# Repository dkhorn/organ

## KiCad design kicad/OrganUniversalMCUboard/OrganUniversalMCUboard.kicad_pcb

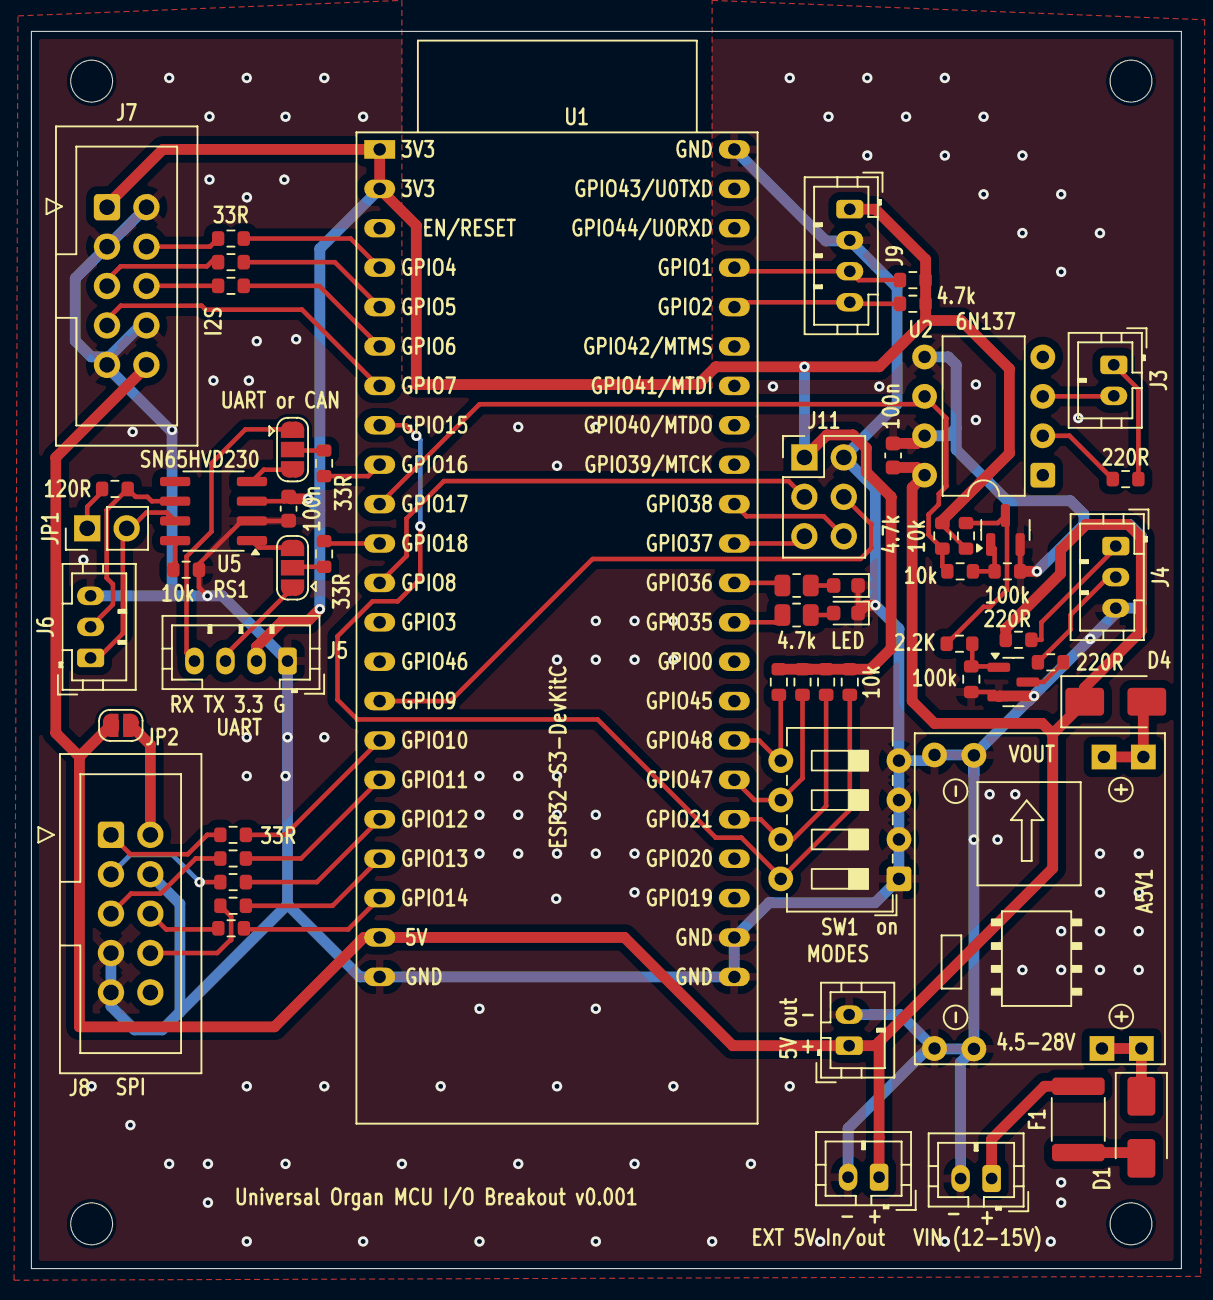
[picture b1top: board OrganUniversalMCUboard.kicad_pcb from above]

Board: 2 copper layers, 74.1 x 79.8 mm, 58 parts (0 on the bottom side), 61 nets.

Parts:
A5V1: 4.7; MP1584EN_Module
CD_U2, CD_U5: 100n; C_0603_1608Metric
D1: SS34; D_SMA
D2, D3: LED; LED_0603_1608Metric
D4: SS14; D_SMA
F1: MF-MSMF050; Fuse_1812_4532Metric
J1: VIN (12-15V); JST_PH_B2B-PH-K_1x02_P2.00mm_Vertical
J2: EXT 5V In/out; JST_PH_B2B-PH-K_1x02_P2.00mm_Vertical
J3: MIDI IN; JST_PH_B2B-PH-K_1x02_P2.00mm_Vertical
J4: MIDI_THRU; JST_PH_B3B-PH-K_1x03_P2.00mm_Vertical
J5: UART; JST_PH_B4B-PH-K_1x04_P2.00mm_Vertical
J6: CAN; JST_PH_B3B-PH-K_1x03_P2.00mm_Vertical
J7: I2S; IDC-Header_2x05_P2.54mm_Vertical
J8: SPI; IDC-Header_2x05_P2.54mm_Vertical
J9: I2C; JST_PH_B4B-PH-K_1x04_P2.00mm_Vertical
J10: 5V out; JST_PH_B2B-PH-K_1x02_P2.00mm_Vertical
J11: GPIO; PinHeader_2x03_P2.54mm_Vertical
JP1: CAN Terminator; PinHeader_1x02_P2.54mm_Vertical
JP2: SolderJumper_2_Open; SolderJumper-2_P1.3mm_Open_RoundedPad1.0x1.5mm
Q1, Q2: MMBT3904; SOT-23
R1, R8: 10k; R_0603_1608Metric
R2, R5, R7: 220R; R_0603_1608Metric
R3: 2.2K; R_0603_1608Metric
R4, R9: 100k; R_0603_1608Metric
R6: 4.7k; R_0603_1608Metric
RLED1, RLED2: 4.7k; R_0805_2012Metric
RP_DIP1, RP_DIP2, RP_DIP3, RP_DIP4: 10k; R_0603_1608Metric
RP_SCL1: 4.7k; R_0603_1608Metric
RP_SDA1: 4.7k; R_0603_1608Metric
RS1: 10k; R_0603_1608Metric
RS_BCLK1: 33R; R_0603_1608Metric
RS_CLR1: 33R; R_0603_1608Metric
RS_DIN1: 33R; R_0603_1608Metric
RS_LATCH1: 33R; R_0603_1608Metric
RS_LRCLK1: 33R; R_0603_1608Metric
RS_MOSI1: 33R; R_0603_1608Metric
RS_OE_N1: 33R; R_0603_1608Metric
RS_SCK1: 33R; R_0603_1608Metric
RS_UART_RX1: 33R; R_0603_1608Metric
RS_UART_TX1: 33R; R_0603_1608Metric
R_TERM1: 120R; R_0603_1608Metric
SJ_COMM_RX1: UART or CAN; SolderJumper-3_P1.3mm_Open_RoundedPad1.0x1.5mm
SJ_COMM_TX1: UART or CAN; SolderJumper-3_P1.3mm_Open_RoundedPad1.0x1.5mm
SW1: MODES; SW_DIP_SPSTx04_Slide_6.7x11.72mm_W7.62mm_P2.54mm_LowProfile
U1: ESP32-S3-DevKitC
U2: 6N137; DIP-8_W7.62mm
U5: SN65HVD230; SOIC-8_3.9x4.9mm_P1.27mm

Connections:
+3.3V: CD_U5.1, J5.2, J7.1, J9.1, J11.1, R6.1, R8.1, RP_DIP1.1, RP_DIP2.1, RP_DIP3.1, RP_DIP4.1, RP_SCL1.1, RP_SDA1.1, U1.1 (3V3), U1.2 (3V3), U5.3 (VCC)
/BoardToBoardComms/CANH: J6.1, JP1.2 (B), U5.7 (CANH)
/BoardToBoardComms/CANL: J6.2, R_TERM1.2, U5.6 (CANL)
/BoardToBoardComms/CAN_RXD: SJ_COMM_RX1.3 (B), U5.4 (R)
/BoardToBoardComms/CAN_TXD: SJ_COMM_TX1.3 (B), U5.1 (D)
/BoardToBoardComms/UART_RX_HDR: J5.4, SJ_COMM_RX1.1 (A)
/BoardToBoardComms/UART_TX_HDR: J5.3, SJ_COMM_TX1.1 (A)
/COMM_RX: RS_UART_RX1.1, U1.9 (GPIO16/ADC2_CH5/32K_N)
/COMM_TX: RS_UART_TX1.1, U1.11 (GPIO18/ADC2_CH7)
/DIP1: RP_DIP1.2, SW1.8, U1.8 (GPIO15/ADC2_CH4/32K_P)
/DIP2: RP_DIP2.2, SW1.7, U1.27 (GPIO21)
/DIP3: RP_DIP3.2, SW1.6, U1.28 (GPIO47)
/DIP4: RP_DIP4.2, SW1.5, U1.29 (GPIO48)
/GPIO8: J11.3, U1.12 (GPIO8/ADC1_CH7)
/GPIO9: J11.4, U1.15 (GPIO9/ADC1_CH8)
/GPIO37: J11.5, U1.34 (GPIO37)
/GPIO38: J11.6, U1.35 (GPIO38)
/I2C_SCL: J9.4, RP_SCL1.2, U1.40 (GPIO2/ADC1_CH1)
/I2C_SDA: J9.3, RP_SDA1.2, U1.41 (GPIO1/ADC1_CH0)
/I2S_BLCK: RS_BCLK1.2, U1.4 (GPIO4/ADC1_CH3)
/I2S_DIN: RS_DIN1.2, U1.6 (GPIO6/ADC1_CH5)
/I2S_LRCLK: RS_LRCLK1.2, U1.5 (GPIO5/ADC1_CH4)
/I2S_MCLK: J7.7, U1.7 (GPIO7/ADC1_CH6)
/LED1: RLED1.1, U1.32 (GPIO35)
/LED2: RLED2.1, U1.33 (GPIO36)
/MIDI/MIDI_IN_P4: J3.1, R5.1
/MIDI/MIDI_IN_P5: J3.2, U2.3 (C)
/MIDI/MIDI_THRU_DRV: Q2.3 (C), R3.1, R8.2
/MIDI/MIDI_THRU_P4: J4.1, R7.2
/MIDI/MIDI_THRU_P5: J4.2, R2.2
/MIDI/MIDI_THRU_SINK: Q1.3 (C), R2.1
/MIDI/Q1_B: Q1.1 (B), R3.2, R4.2
/MIDI_GPIO: R1.1, R6.2, U1.10 (GPIO17/ADC2_CH6), U2.6 (VO)
/Power/BUCK_5V: A5V1.3 (OUT+), D4.2 (A)
/Power/VIN_12V: F1.2, J1.1
/Power/VIN_FUSED: D1.2 (A), F1.1
/Power/VIN_PROT: A5V1.1 (IN+), D1.1 (K)
/SPI_CLR: RS_CLR1.2, U1.16 (GPIO10/ADC1_CH9)
/SPI_LATCH: RS_LATCH1.2, U1.20 (GPIO14/ADC2_CH3)
/SPI_MOSI: RS_MOSI1.2, U1.19 (GPIO13/ADC2_CH2)
/SPI_OE_N: RS_OE_N1.2, U1.17 (GPIO11/ADC2_CH0)
/SPI_SCK: RS_SCK1.2, U1.18 (GPIO12/ADC2_CH1)
GND: A5V1.2 (IN-), A5V1.4 (OUT-), CD_U2.2, CD_U5.2, D2.1 (K), D3.1 (K), J1.2, J2.2, J4.3, J5.1, J6.3, J7.2, J7.3, J7.8, J7.9, J8.4, J8.7, J8.9, J9.2, J10.2, J11.2, Q1.2 (E), Q2.2 (E), R4.1, R9.1, RS1.2, SW1.1, SW1.2, SW1.3, SW1.4, U1.22 (GND), U1.23 (GND), U1.24 (GND), U1.44 (GND), U2.5 (GND), U2.7 (EN), U5.2 (GND)
unnamed: D2.2 (A), RLED1.2
unnamed: D3.2 (A), RLED2.2
unnamed: J7.4, RS_BCLK1.1
unnamed: J7.5, RS_LRCLK1.1
unnamed: J7.6, RS_DIN1.1
unnamed: J8.1, RS_CLR1.1
unnamed: J8.2, JP2.1 (A)
unnamed: J8.3, RS_SCK1.1
unnamed: J8.5, RS_OE_N1.1
unnamed: J8.6, RS_LATCH1.1
unnamed: J8.8, RS_MOSI1.1
unnamed: JP1.1 (A), R_TERM1.1
unnamed: Q2.1 (B), R1.2, R9.2
unnamed: RS_UART_RX1.2, SJ_COMM_RX1.2 (C)
unnamed: RS_UART_TX1.2, SJ_COMM_TX1.2 (C)
unnamed: R5.2, U2.2 (A)
unnamed: RS1.1, U5.8 (Rs)
SYS_5V: CD_U2.1, D4.1 (K), J2.1, J7.10, J10.1, JP2.2 (B), R7.1, U1.21 (5V), U2.8 (VCC)

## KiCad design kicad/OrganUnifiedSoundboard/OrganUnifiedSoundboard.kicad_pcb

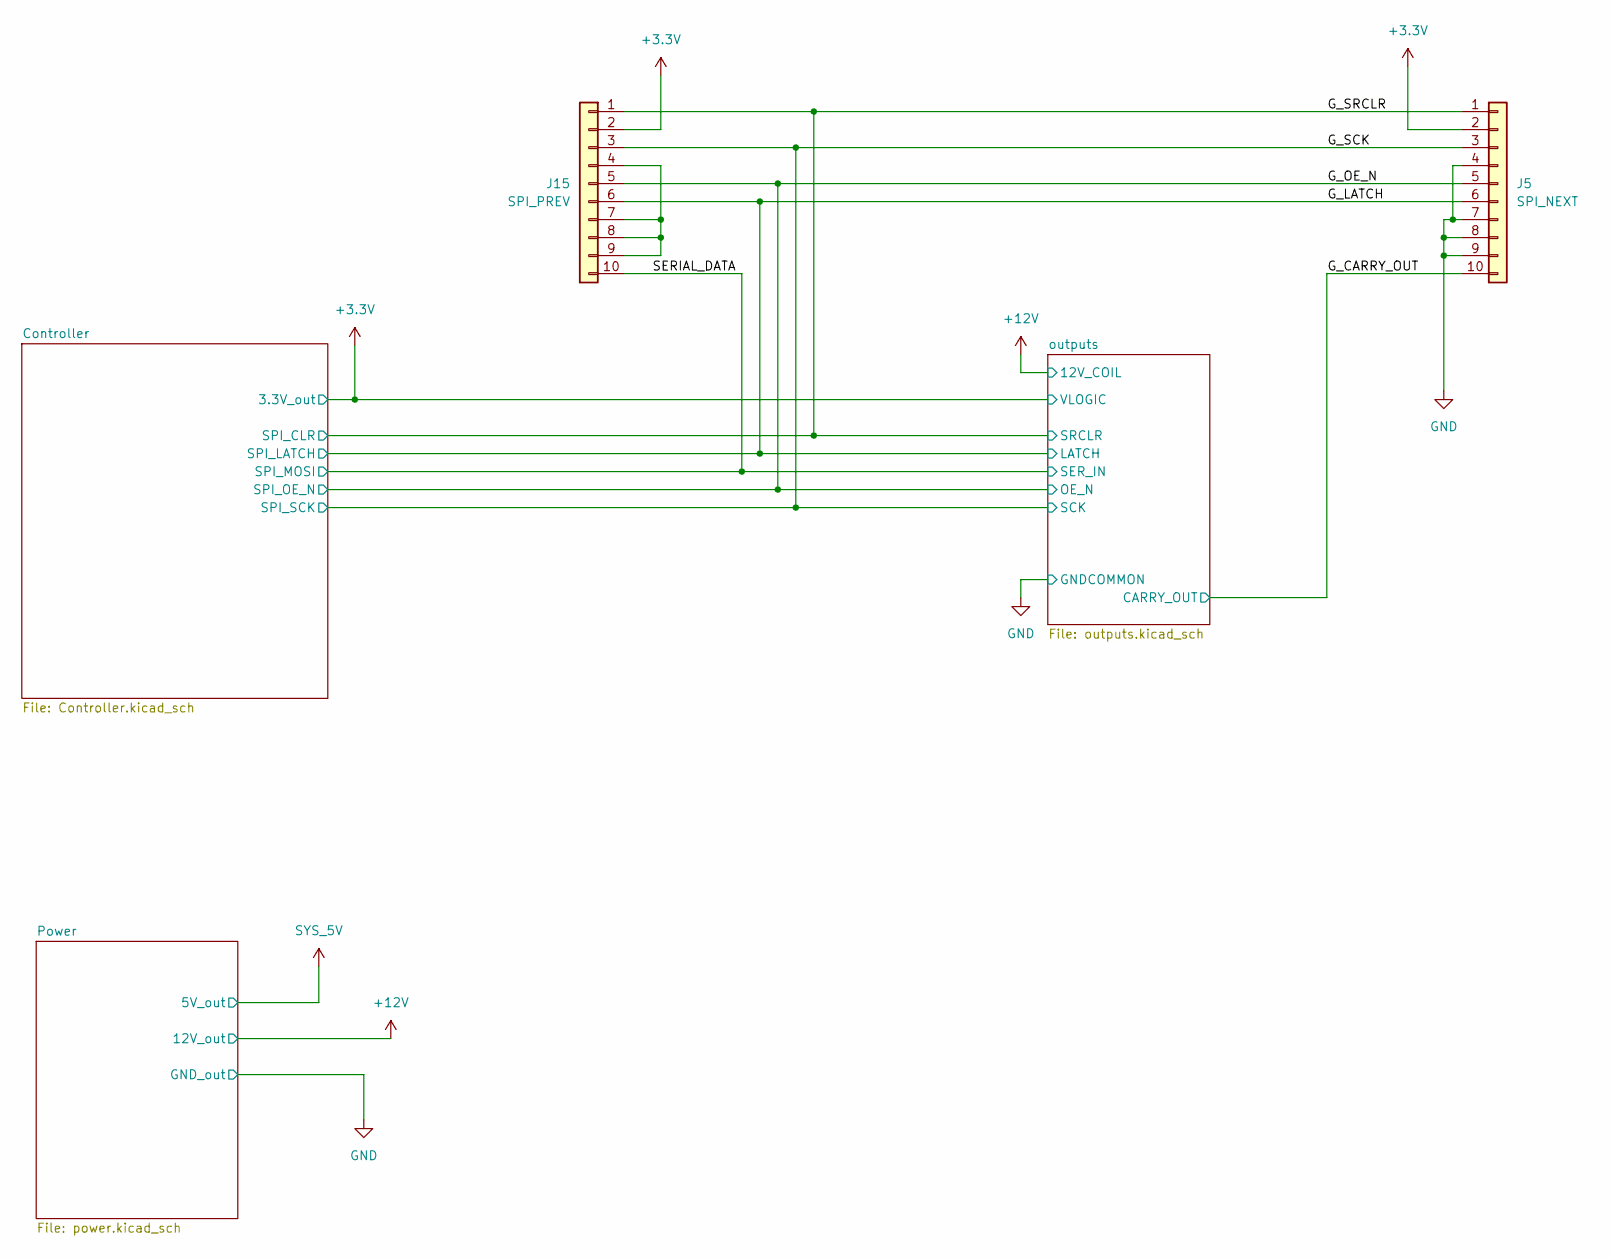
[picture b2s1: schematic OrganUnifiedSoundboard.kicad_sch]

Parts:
J5: SPI_NEXT; IDC-Header_2x05_P2.54mm_Vertical
J15: SPI_PREV; IDC-Header_2x05_P2.54mm_Vertical

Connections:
+3.3V: J5.2, J15.2; also elsewhere on the board
/G_CARRY_OUT: J5.10; also elsewhere on the board
/G_LATCH: J5.6, J15.6; also elsewhere on the board
/G_OE_N: J5.5, J15.5; also elsewhere on the board
/G_SCK: J5.3, J15.3; also elsewhere on the board
/G_SRCLR: J5.1, J15.1; also elsewhere on the board
/SERIAL_DATA: J15.10; also elsewhere on the board
GND: J5.4, J5.7, J5.8, J5.9; also elsewhere on the board
unnamed: J15.4, J15.7, J15.8, J15.9

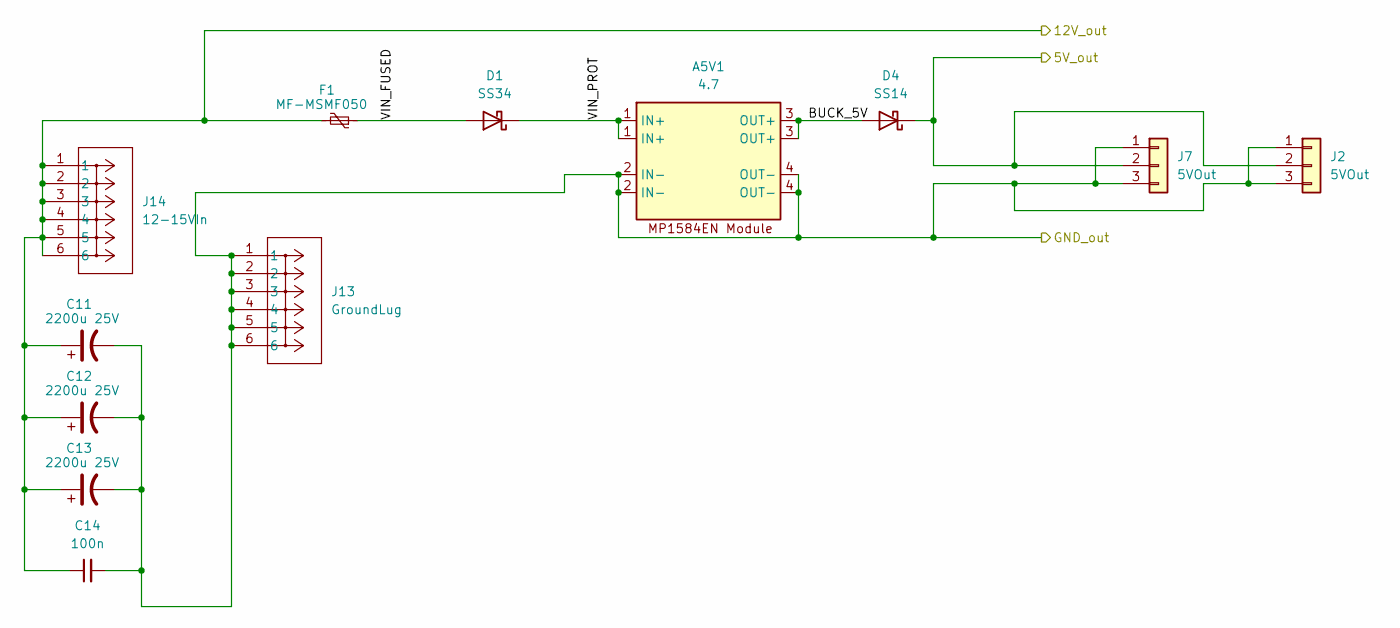
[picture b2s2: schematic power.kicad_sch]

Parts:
A5V1: 4.7; MP1584EN_Module
C11, C12, C13: 2200u 25V; CP_Radial_D10.0mm_P5.00mm
C14: 100n; C_0603_1608Metric
D1: SS34; D_SMA
D4: SS14; D_SMA
F1: MF-MSMF050; Fuse_1812_4532Metric
J2, J7: 5VOut; JST_PH_B3B-PH-K_1x03_P2.00mm_Vertical
J13: GroundLug; CONN_8199_KEY
J14: 12-15VIn; CONN_8199_KEY

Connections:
+12V: C11.1, C12.1, C13.1, C14.1, F1.2, J14.1, J14.2, J14.3, J14.4, J14.5, J14.6; also elsewhere on the board
/Power/BUCK_5V: A5V1.3 (OUT+), D4.2 (A)
/Power/VIN_FUSED: D1.2 (A), F1.1
/Power/VIN_PROT: A5V1.1 (IN+), D1.1 (K)
GND: A5V1.2 (IN-), A5V1.4 (OUT-), C11.2, C12.2, C13.2, C14.2, J2.1, J2.3, J7.1, J7.3, J13.1, J13.2, J13.3, J13.4, J13.5, J13.6; also elsewhere on the board
SYS_5V: D4.1 (K), J2.2, J7.2; also elsewhere on the board

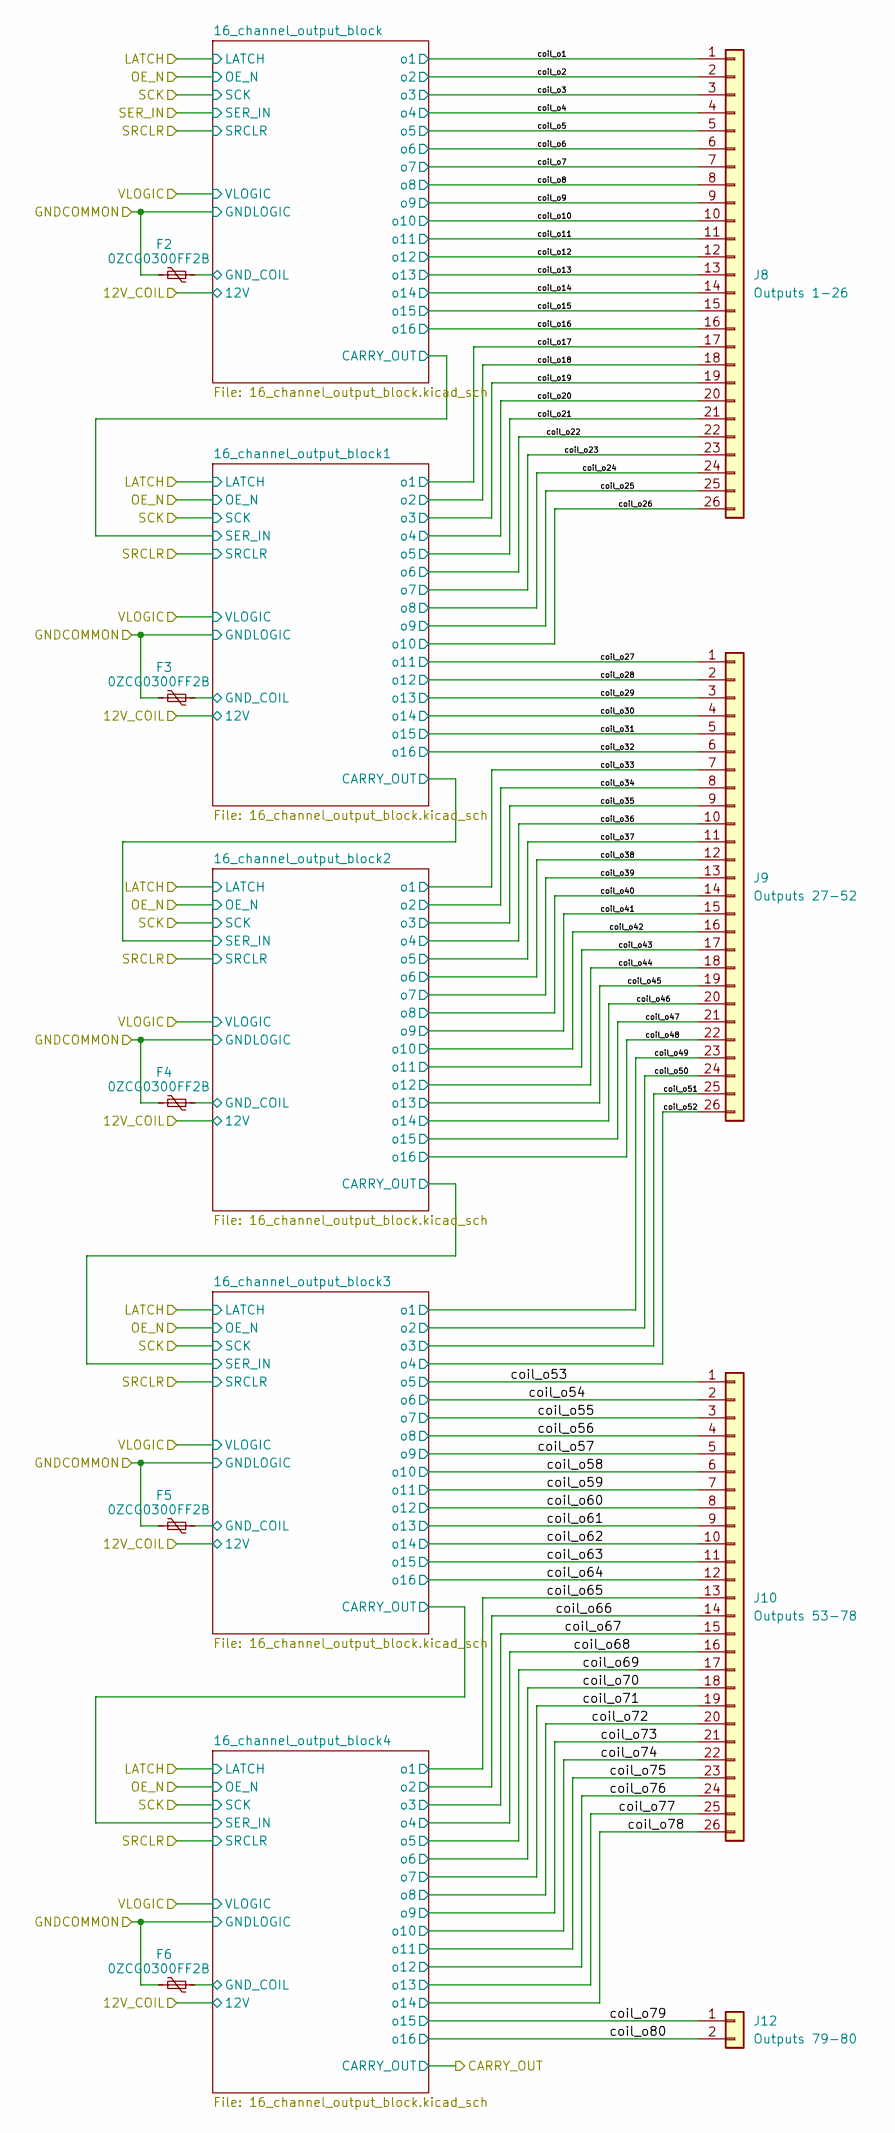
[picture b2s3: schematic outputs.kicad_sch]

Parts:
F2, F3, F4, F5, F6: 0ZCG0300FF2B; Fuse_1812_4532Metric
J8: Outputs 1-26; IDC-Header_2x13_P2.54mm_Vertical
J9: Outputs 27-52; IDC-Header_2x13_P2.54mm_Vertical
J10: Outputs 53-78; IDC-Header_2x13_P2.54mm_Vertical
J12: Outputs 79-80; JST_PH_B2B-PH-K_1x02_P2.00mm_Vertical

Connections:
/outputs/16_channel_output_block1/GND_COIL: F3.1; also elsewhere on the board
/outputs/16_channel_output_block2/GND_COIL: F4.1; also elsewhere on the board
/outputs/16_channel_output_block3/GND_COIL: F5.1; also elsewhere on the board
/outputs/16_channel_output_block4/GND_COIL: F6.1; also elsewhere on the board
/outputs/16_channel_output_block/GND_COIL: F2.1; also elsewhere on the board
/outputs/coil_o1: J8.1; also elsewhere on the board
/outputs/coil_o2: J8.2; also elsewhere on the board
/outputs/coil_o3: J8.3; also elsewhere on the board
/outputs/coil_o4: J8.4; also elsewhere on the board
/outputs/coil_o5: J8.5; also elsewhere on the board
/outputs/coil_o6: J8.6; also elsewhere on the board
/outputs/coil_o7: J8.7; also elsewhere on the board
/outputs/coil_o8: J8.8; also elsewhere on the board
/outputs/coil_o9: J8.9; also elsewhere on the board
/outputs/coil_o10: J8.10; also elsewhere on the board
/outputs/coil_o11: J8.11; also elsewhere on the board
/outputs/coil_o12: J8.12; also elsewhere on the board
/outputs/coil_o13: J8.13; also elsewhere on the board
/outputs/coil_o14: J8.14; also elsewhere on the board
/outputs/coil_o15: J8.15; also elsewhere on the board
/outputs/coil_o16: J8.16; also elsewhere on the board
/outputs/coil_o17: J8.17; also elsewhere on the board
/outputs/coil_o18: J8.18; also elsewhere on the board
/outputs/coil_o19: J8.19; also elsewhere on the board
/outputs/coil_o20: J8.20; also elsewhere on the board
/outputs/coil_o21: J8.21; also elsewhere on the board
/outputs/coil_o22: J8.22; also elsewhere on the board
/outputs/coil_o23: J8.23; also elsewhere on the board
/outputs/coil_o24: J8.24; also elsewhere on the board
/outputs/coil_o25: J8.25; also elsewhere on the board
/outputs/coil_o26: J8.26; also elsewhere on the board
/outputs/coil_o27: J9.1; also elsewhere on the board
/outputs/coil_o28: J9.2; also elsewhere on the board
/outputs/coil_o29: J9.3; also elsewhere on the board
/outputs/coil_o30: J9.4; also elsewhere on the board
/outputs/coil_o31: J9.5; also elsewhere on the board
/outputs/coil_o32: J9.6; also elsewhere on the board
/outputs/coil_o33: J9.7; also elsewhere on the board
/outputs/coil_o34: J9.8; also elsewhere on the board
/outputs/coil_o35: J9.9; also elsewhere on the board
/outputs/coil_o36: J9.10; also elsewhere on the board
/outputs/coil_o37: J9.11; also elsewhere on the board
/outputs/coil_o38: J9.12; also elsewhere on the board
/outputs/coil_o39: J9.13; also elsewhere on the board
/outputs/coil_o40: J9.14; also elsewhere on the board
/outputs/coil_o41: J9.15; also elsewhere on the board
/outputs/coil_o42: J9.16; also elsewhere on the board
/outputs/coil_o43: J9.17; also elsewhere on the board
/outputs/coil_o44: J9.18; also elsewhere on the board
/outputs/coil_o45: J9.19; also elsewhere on the board
/outputs/coil_o46: J9.20; also elsewhere on the board
/outputs/coil_o47: J9.21; also elsewhere on the board
/outputs/coil_o48: J9.22; also elsewhere on the board
/outputs/coil_o49: J9.23; also elsewhere on the board
/outputs/coil_o50: J9.24; also elsewhere on the board
/outputs/coil_o51: J9.25; also elsewhere on the board
/outputs/coil_o52: J9.26; also elsewhere on the board
/outputs/coil_o53: J10.1; also elsewhere on the board
/outputs/coil_o54: J10.2; also elsewhere on the board
/outputs/coil_o55: J10.3; also elsewhere on the board
/outputs/coil_o56: J10.4; also elsewhere on the board
/outputs/coil_o57: J10.5; also elsewhere on the board
/outputs/coil_o58: J10.6; also elsewhere on the board
/outputs/coil_o59: J10.7; also elsewhere on the board
/outputs/coil_o60: J10.8; also elsewhere on the board
/outputs/coil_o61: J10.9; also elsewhere on the board
/outputs/coil_o62: J10.10; also elsewhere on the board
/outputs/coil_o63: J10.11; also elsewhere on the board
/outputs/coil_o64: J10.12; also elsewhere on the board
/outputs/coil_o65: J10.13; also elsewhere on the board
/outputs/coil_o66: J10.14; also elsewhere on the board
/outputs/coil_o67: J10.15; also elsewhere on the board
/outputs/coil_o68: J10.16; also elsewhere on the board
/outputs/coil_o69: J10.17; also elsewhere on the board
/outputs/coil_o70: J10.18; also elsewhere on the board
/outputs/coil_o71: J10.19; also elsewhere on the board
/outputs/coil_o72: J10.20; also elsewhere on the board
/outputs/coil_o73: J10.21; also elsewhere on the board
/outputs/coil_o74: J10.22; also elsewhere on the board
/outputs/coil_o75: J10.23; also elsewhere on the board
/outputs/coil_o76: J10.24; also elsewhere on the board
/outputs/coil_o77: J10.25; also elsewhere on the board
/outputs/coil_o78: J10.26; also elsewhere on the board
/outputs/coil_o79: J12.1; also elsewhere on the board
/outputs/coil_o80: J12.2; also elsewhere on the board
GND: F2.2, F3.2, F4.2, F5.2, F6.2; also elsewhere on the board

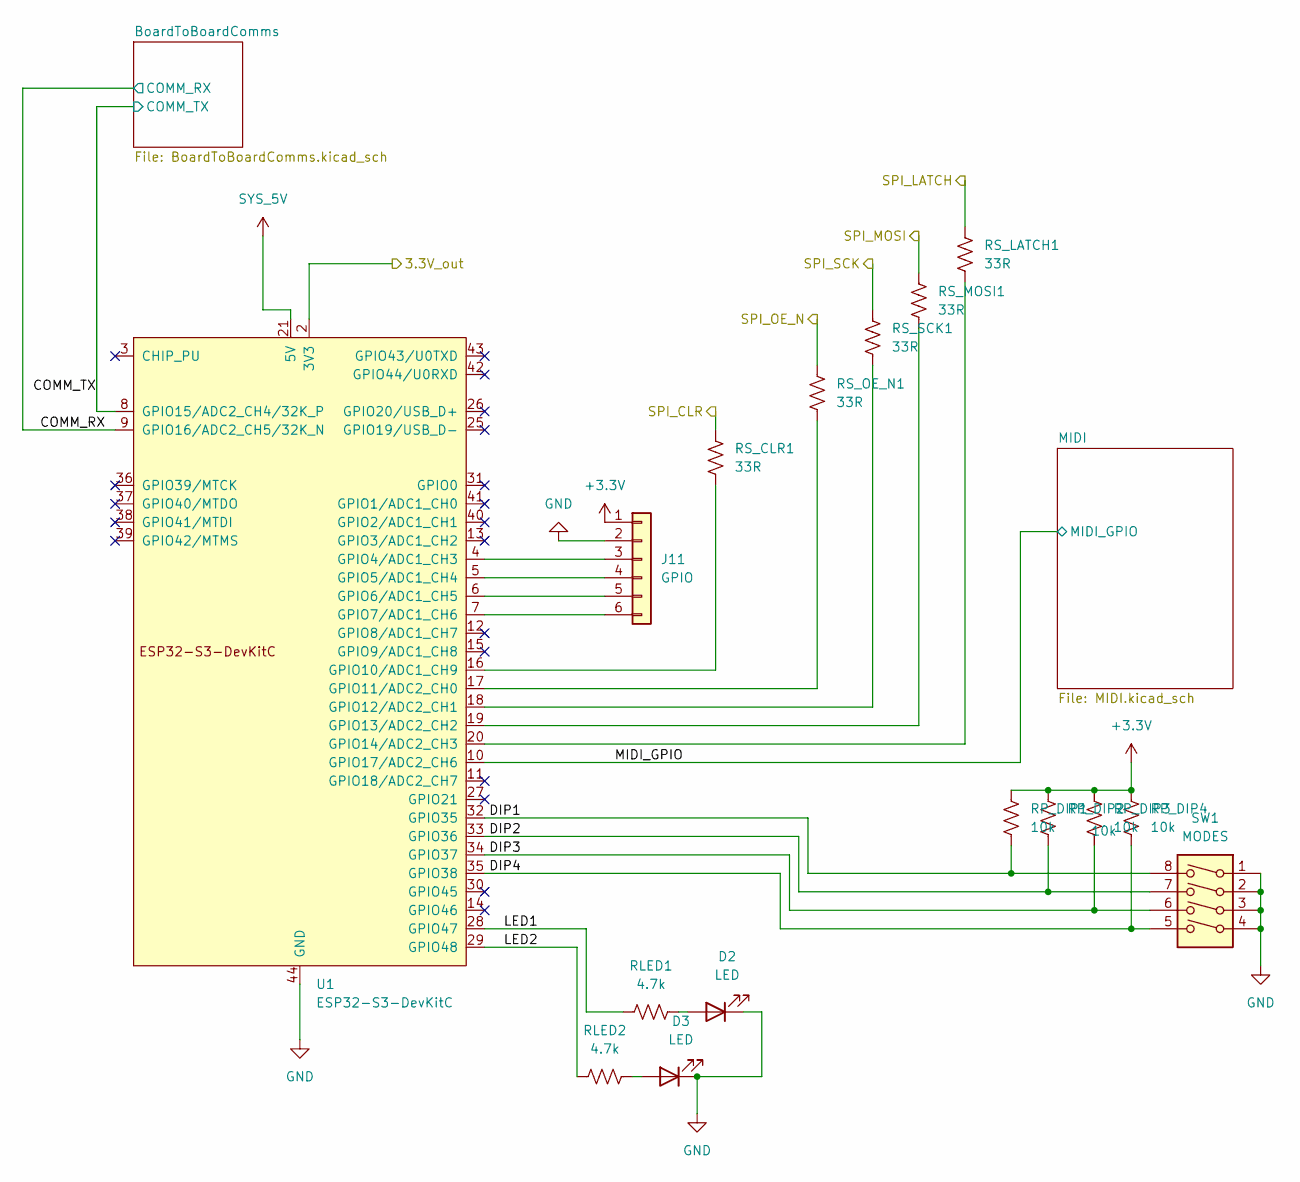
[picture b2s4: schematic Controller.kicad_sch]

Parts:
D2, D3: LED; LED_0603_1608Metric
J11: GPIO; PinHeader_2x03_P2.54mm_Vertical
RLED1, RLED2: 4.7k; R_0805_2012Metric
RP_DIP1, RP_DIP2, RP_DIP3, RP_DIP4: 10k; R_0603_1608Metric
RS_CLR1: 33R; R_0603_1608Metric
RS_LATCH1: 33R; R_0603_1608Metric
RS_MOSI1: 33R; R_0603_1608Metric
RS_OE_N1: 33R; R_0603_1608Metric
RS_SCK1: 33R; R_0603_1608Metric
SW1: MODES; SW_DIP_SPSTx04_Slide_6.7x11.72mm_W7.62mm_P2.54mm_LowProfile
U1: ESP32-S3-DevKitC

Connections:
+3.3V: J11.1, RP_DIP1.1, RP_DIP2.1, RP_DIP3.1, RP_DIP4.1, U1.1 (3V3), U1.2 (3V3); also elsewhere on the board
/Controller/COMM_RX: U1.9 (GPIO16/ADC2_CH5/32K_N); also elsewhere on the board
/Controller/COMM_TX: U1.8 (GPIO15/ADC2_CH4/32K_P); also elsewhere on the board
/Controller/DIP1: RP_DIP1.2, SW1.8, U1.32 (GPIO35)
/Controller/DIP2: RP_DIP2.2, SW1.7, U1.33 (GPIO36)
/Controller/DIP3: RP_DIP3.2, SW1.6, U1.34 (GPIO37)
/Controller/DIP4: RP_DIP4.2, SW1.5, U1.35 (GPIO38)
/Controller/LED1: RLED1.1, U1.28 (GPIO47)
/Controller/LED2: RLED2.1, U1.29 (GPIO48)
/Controller/MIDI_GPIO: U1.10 (GPIO17/ADC2_CH6); also elsewhere on the board
/G_LATCH: RS_LATCH1.1; also elsewhere on the board
/G_OE_N: RS_OE_N1.1; also elsewhere on the board
/G_SCK: RS_SCK1.1; also elsewhere on the board
/G_SRCLR: RS_CLR1.1; also elsewhere on the board
/SERIAL_DATA: RS_MOSI1.1; also elsewhere on the board
GND: D2.1 (K), D3.1 (K), J11.2, SW1.1, SW1.2, SW1.3, SW1.4, U1.22 (GND), U1.23 (GND), U1.24 (GND), U1.44 (GND); also elsewhere on the board
unnamed: D2.2 (A), RLED1.2
unnamed: D3.2 (A), RLED2.2
unnamed: J11.3, U1.4 (GPIO4/ADC1_CH3)
unnamed: J11.4, U1.5 (GPIO5/ADC1_CH4)
unnamed: J11.5, U1.6 (GPIO6/ADC1_CH5)
unnamed: J11.6, U1.7 (GPIO7/ADC1_CH6)
unnamed: RS_CLR1.2, U1.16 (GPIO10/ADC1_CH9)
unnamed: RS_OE_N1.2, U1.17 (GPIO11/ADC2_CH0)
unnamed: RS_SCK1.2, U1.18 (GPIO12/ADC2_CH1)
unnamed: RS_MOSI1.2, U1.19 (GPIO13/ADC2_CH2)
unnamed: RS_LATCH1.2, U1.20 (GPIO14/ADC2_CH3)
SYS_5V: U1.21 (5V); also elsewhere on the board

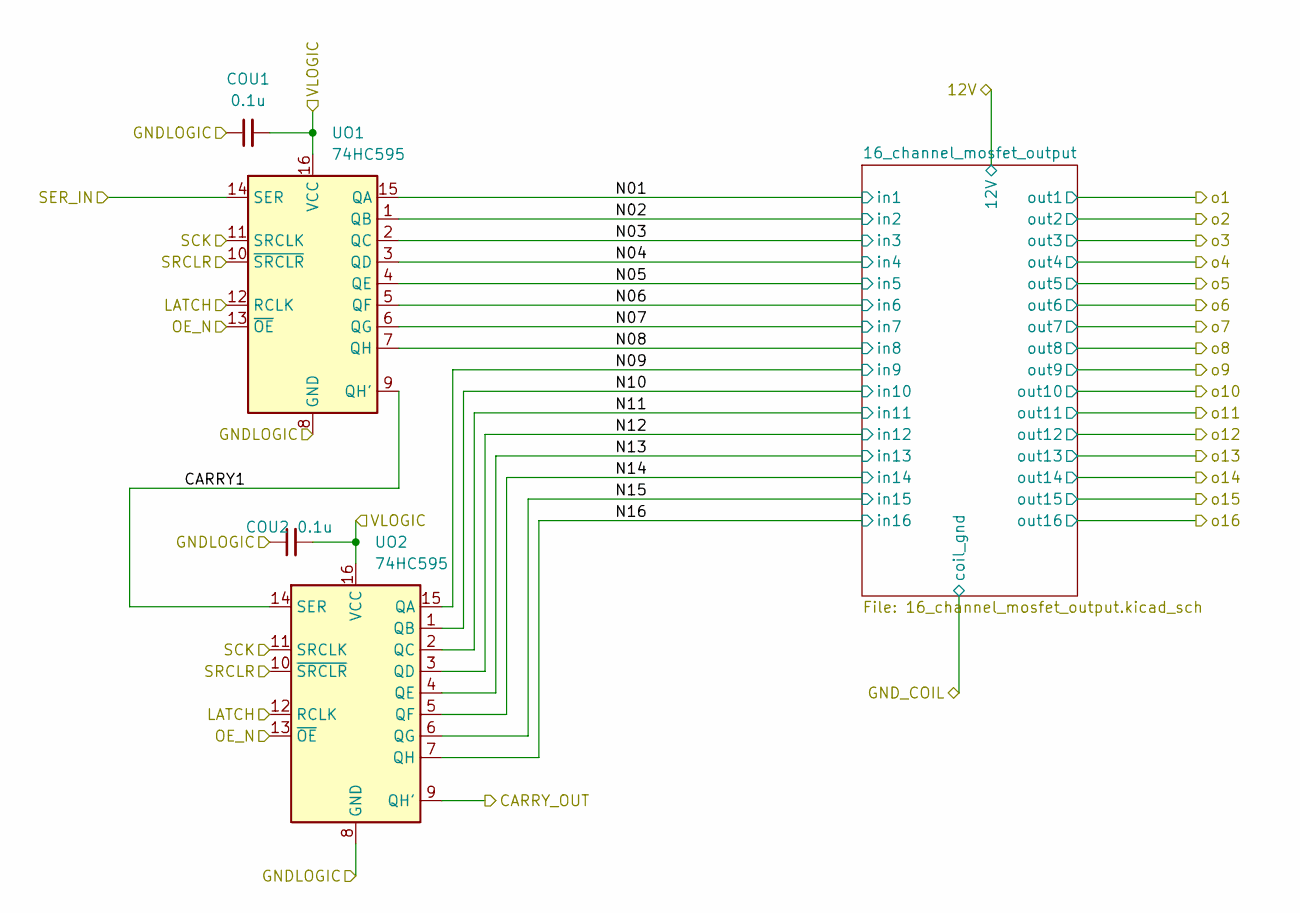
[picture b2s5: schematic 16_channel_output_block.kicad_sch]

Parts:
COU1, COU2: 0.1u; C_0805_2012Metric
UO1, UO2: 74HC595; SOP-16_3.9x9.9mm_P1.27mm

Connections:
+3.3V: COU1.2, COU2.2, UO1.16 (VCC), UO2.16 (VCC); also elsewhere on the board
/G_LATCH: UO1.12 (RCLK), UO2.12 (RCLK); also elsewhere on the board
/G_OE_N: UO1.13 (~OE), UO2.13 (~OE); also elsewhere on the board
/G_SCK: UO1.11 (SRCLK), UO2.11 (SRCLK); also elsewhere on the board
/G_SRCLR: UO1.10 (~SRCLR), UO2.10 (~SRCLR); also elsewhere on the board
/SERIAL_DATA: UO1.14 (SER); also elsewhere on the board
/outputs/16_channel_output_block/CARRY1: UO1.9 (QH'), UO2.14 (SER)
/outputs/16_channel_output_block/CARRY_OUT: UO2.9 (QH'); also elsewhere on the board
/outputs/16_channel_output_block/N01: UO1.15 (QA); also elsewhere on the board
/outputs/16_channel_output_block/N02: UO1.1 (QB); also elsewhere on the board
/outputs/16_channel_output_block/N03: UO1.2 (QC); also elsewhere on the board
/outputs/16_channel_output_block/N04: UO1.3 (QD); also elsewhere on the board
/outputs/16_channel_output_block/N05: UO1.4 (QE); also elsewhere on the board
/outputs/16_channel_output_block/N06: UO1.5 (QF); also elsewhere on the board
/outputs/16_channel_output_block/N07: UO1.6 (QG); also elsewhere on the board
/outputs/16_channel_output_block/N08: UO1.7 (QH); also elsewhere on the board
/outputs/16_channel_output_block/N09: UO2.15 (QA); also elsewhere on the board
/outputs/16_channel_output_block/N10: UO2.1 (QB); also elsewhere on the board
/outputs/16_channel_output_block/N11: UO2.2 (QC); also elsewhere on the board
/outputs/16_channel_output_block/N12: UO2.3 (QD); also elsewhere on the board
/outputs/16_channel_output_block/N13: UO2.4 (QE); also elsewhere on the board
/outputs/16_channel_output_block/N14: UO2.5 (QF); also elsewhere on the board
/outputs/16_channel_output_block/N15: UO2.6 (QG); also elsewhere on the board
/outputs/16_channel_output_block/N16: UO2.7 (QH); also elsewhere on the board
GND: COU1.1, COU2.1, UO1.8 (GND), UO2.8 (GND); also elsewhere on the board

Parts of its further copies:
COU3, COU4, COU5, COU6, COU7, COU8, COU9, COU10: 0.1u; C_0805_2012Metric
UO3, UO4, UO5, UO6, UO7, UO8, UO9, UO10: 74HC595; SOP-16_3.9x9.9mm_P1.27mm

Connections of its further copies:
+3.3V: COU3.2, COU4.2, COU5.2, COU6.2, COU7.2, COU8.2, COU9.2, COU10.2, UO3.16 (VCC), UO4.16 (VCC), UO5.16 (VCC), UO6.16 (VCC), UO7.16 (VCC), UO8.16 (VCC), UO9.16 (VCC), UO10.16 (VCC); also elsewhere on the board
/G_CARRY_OUT: UO10.9 (QH'); also elsewhere on the board
/G_LATCH: UO3.12 (RCLK), UO4.12 (RCLK), UO5.12 (RCLK), UO6.12 (RCLK), UO7.12 (RCLK), UO8.12 (RCLK), UO9.12 (RCLK), UO10.12 (RCLK); also elsewhere on the board
/G_OE_N: UO3.13 (~OE), UO4.13 (~OE), UO5.13 (~OE), UO6.13 (~OE), UO7.13 (~OE), UO8.13 (~OE), UO9.13 (~OE), UO10.13 (~OE); also elsewhere on the board
/G_SCK: UO3.11 (SRCLK), UO4.11 (SRCLK), UO5.11 (SRCLK), UO6.11 (SRCLK), UO7.11 (SRCLK), UO8.11 (SRCLK), UO9.11 (SRCLK), UO10.11 (SRCLK); also elsewhere on the board
/G_SRCLR: UO3.10 (~SRCLR), UO4.10 (~SRCLR), UO5.10 (~SRCLR), UO6.10 (~SRCLR), UO7.10 (~SRCLR), UO8.10 (~SRCLR), UO9.10 (~SRCLR), UO10.10 (~SRCLR); also elsewhere on the board
/outputs/16_channel_output_block1/CARRY1: UO3.9 (QH'), UO4.14 (SER)
/outputs/16_channel_output_block1/CARRY_OUT: UO4.9 (QH'), UO5.14 (SER)
/outputs/16_channel_output_block1/N01: UO3.15 (QA); also elsewhere on the board
/outputs/16_channel_output_block1/N02: UO3.1 (QB); also elsewhere on the board
/outputs/16_channel_output_block1/N03: UO3.2 (QC); also elsewhere on the board
/outputs/16_channel_output_block1/N04: UO3.3 (QD); also elsewhere on the board
/outputs/16_channel_output_block1/N05: UO3.4 (QE); also elsewhere on the board
/outputs/16_channel_output_block1/N06: UO3.5 (QF); also elsewhere on the board
/outputs/16_channel_output_block1/N07: UO3.6 (QG); also elsewhere on the board
/outputs/16_channel_output_block1/N08: UO3.7 (QH); also elsewhere on the board
/outputs/16_channel_output_block1/N09: UO4.15 (QA); also elsewhere on the board
/outputs/16_channel_output_block1/N10: UO4.1 (QB); also elsewhere on the board
/outputs/16_channel_output_block1/N11: UO4.2 (QC); also elsewhere on the board
/outputs/16_channel_output_block1/N12: UO4.3 (QD); also elsewhere on the board
/outputs/16_channel_output_block1/N13: UO4.4 (QE); also elsewhere on the board
/outputs/16_channel_output_block1/N14: UO4.5 (QF); also elsewhere on the board
/outputs/16_channel_output_block1/N15: UO4.6 (QG); also elsewhere on the board
/outputs/16_channel_output_block1/N16: UO4.7 (QH); also elsewhere on the board
/outputs/16_channel_output_block2/CARRY1: UO5.9 (QH'), UO6.14 (SER)
/outputs/16_channel_output_block2/CARRY_OUT: UO6.9 (QH'), UO7.14 (SER)
/outputs/16_channel_output_block2/N01: UO5.15 (QA); also elsewhere on the board
/outputs/16_channel_output_block2/N02: UO5.1 (QB); also elsewhere on the board
/outputs/16_channel_output_block2/N03: UO5.2 (QC); also elsewhere on the board
/outputs/16_channel_output_block2/N04: UO5.3 (QD); also elsewhere on the board
/outputs/16_channel_output_block2/N05: UO5.4 (QE); also elsewhere on the board
/outputs/16_channel_output_block2/N06: UO5.5 (QF); also elsewhere on the board
/outputs/16_channel_output_block2/N07: UO5.6 (QG); also elsewhere on the board
/outputs/16_channel_output_block2/N08: UO5.7 (QH); also elsewhere on the board
/outputs/16_channel_output_block2/N09: UO6.15 (QA); also elsewhere on the board
/outputs/16_channel_output_block2/N10: UO6.1 (QB); also elsewhere on the board
/outputs/16_channel_output_block2/N11: UO6.2 (QC); also elsewhere on the board
/outputs/16_channel_output_block2/N12: UO6.3 (QD); also elsewhere on the board
/outputs/16_channel_output_block2/N13: UO6.4 (QE); also elsewhere on the board
/outputs/16_channel_output_block2/N14: UO6.5 (QF); also elsewhere on the board
/outputs/16_channel_output_block2/N15: UO6.6 (QG); also elsewhere on the board
/outputs/16_channel_output_block2/N16: UO6.7 (QH); also elsewhere on the board
/outputs/16_channel_output_block3/CARRY1: UO7.9 (QH'), UO8.14 (SER)
/outputs/16_channel_output_block3/CARRY_OUT: UO8.9 (QH'), UO9.14 (SER)
/outputs/16_channel_output_block3/N01: UO7.15 (QA); also elsewhere on the board
/outputs/16_channel_output_block3/N02: UO7.1 (QB); also elsewhere on the board
/outputs/16_channel_output_block3/N03: UO7.2 (QC); also elsewhere on the board
/outputs/16_channel_output_block3/N04: UO7.3 (QD); also elsewhere on the board
/outputs/16_channel_output_block3/N05: UO7.4 (QE); also elsewhere on the board
/outputs/16_channel_output_block3/N06: UO7.5 (QF); also elsewhere on the board
/outputs/16_channel_output_block3/N07: UO7.6 (QG); also elsewhere on the board
/outputs/16_channel_output_block3/N08: UO7.7 (QH); also elsewhere on the board
/outputs/16_channel_output_block3/N09: UO8.15 (QA); also elsewhere on the board
/outputs/16_channel_output_block3/N10: UO8.1 (QB); also elsewhere on the board
/outputs/16_channel_output_block3/N11: UO8.2 (QC); also elsewhere on the board
/outputs/16_channel_output_block3/N12: UO8.3 (QD); also elsewhere on the board
/outputs/16_channel_output_block3/N13: UO8.4 (QE); also elsewhere on the board
/outputs/16_channel_output_block3/N14: UO8.5 (QF); also elsewhere on the board
/outputs/16_channel_output_block3/N15: UO8.6 (QG); also elsewhere on the board
/outputs/16_channel_output_block3/N16: UO8.7 (QH); also elsewhere on the board
/outputs/16_channel_output_block4/CARRY1: UO9.9 (QH'), UO10.14 (SER)
/outputs/16_channel_output_block4/N01: UO9.15 (QA); also elsewhere on the board
/outputs/16_channel_output_block4/N02: UO9.1 (QB); also elsewhere on the board
/outputs/16_channel_output_block4/N03: UO9.2 (QC); also elsewhere on the board
/outputs/16_channel_output_block4/N04: UO9.3 (QD); also elsewhere on the board
/outputs/16_channel_output_block4/N05: UO9.4 (QE); also elsewhere on the board
/outputs/16_channel_output_block4/N06: UO9.5 (QF); also elsewhere on the board
/outputs/16_channel_output_block4/N07: UO9.6 (QG); also elsewhere on the board
/outputs/16_channel_output_block4/N08: UO9.7 (QH); also elsewhere on the board
/outputs/16_channel_output_block4/N09: UO10.15 (QA); also elsewhere on the board
/outputs/16_channel_output_block4/N10: UO10.1 (QB); also elsewhere on the board
/outputs/16_channel_output_block4/N11: UO10.2 (QC); also elsewhere on the board
/outputs/16_channel_output_block4/N12: UO10.3 (QD); also elsewhere on the board
/outputs/16_channel_output_block4/N13: UO10.4 (QE); also elsewhere on the board
/outputs/16_channel_output_block4/N14: UO10.5 (QF); also elsewhere on the board
/outputs/16_channel_output_block4/N15: UO10.6 (QG); also elsewhere on the board
/outputs/16_channel_output_block4/N16: UO10.7 (QH); also elsewhere on the board
/outputs/16_channel_output_block/CARRY_OUT: UO3.14 (SER); also elsewhere on the board
GND: COU3.1, COU4.1, COU5.1, COU6.1, COU7.1, COU8.1, COU9.1, COU10.1, UO3.8 (GND), UO4.8 (GND), UO5.8 (GND), UO6.8 (GND), UO7.8 (GND), UO8.8 (GND), UO9.8 (GND), UO10.8 (GND); also elsewhere on the board
